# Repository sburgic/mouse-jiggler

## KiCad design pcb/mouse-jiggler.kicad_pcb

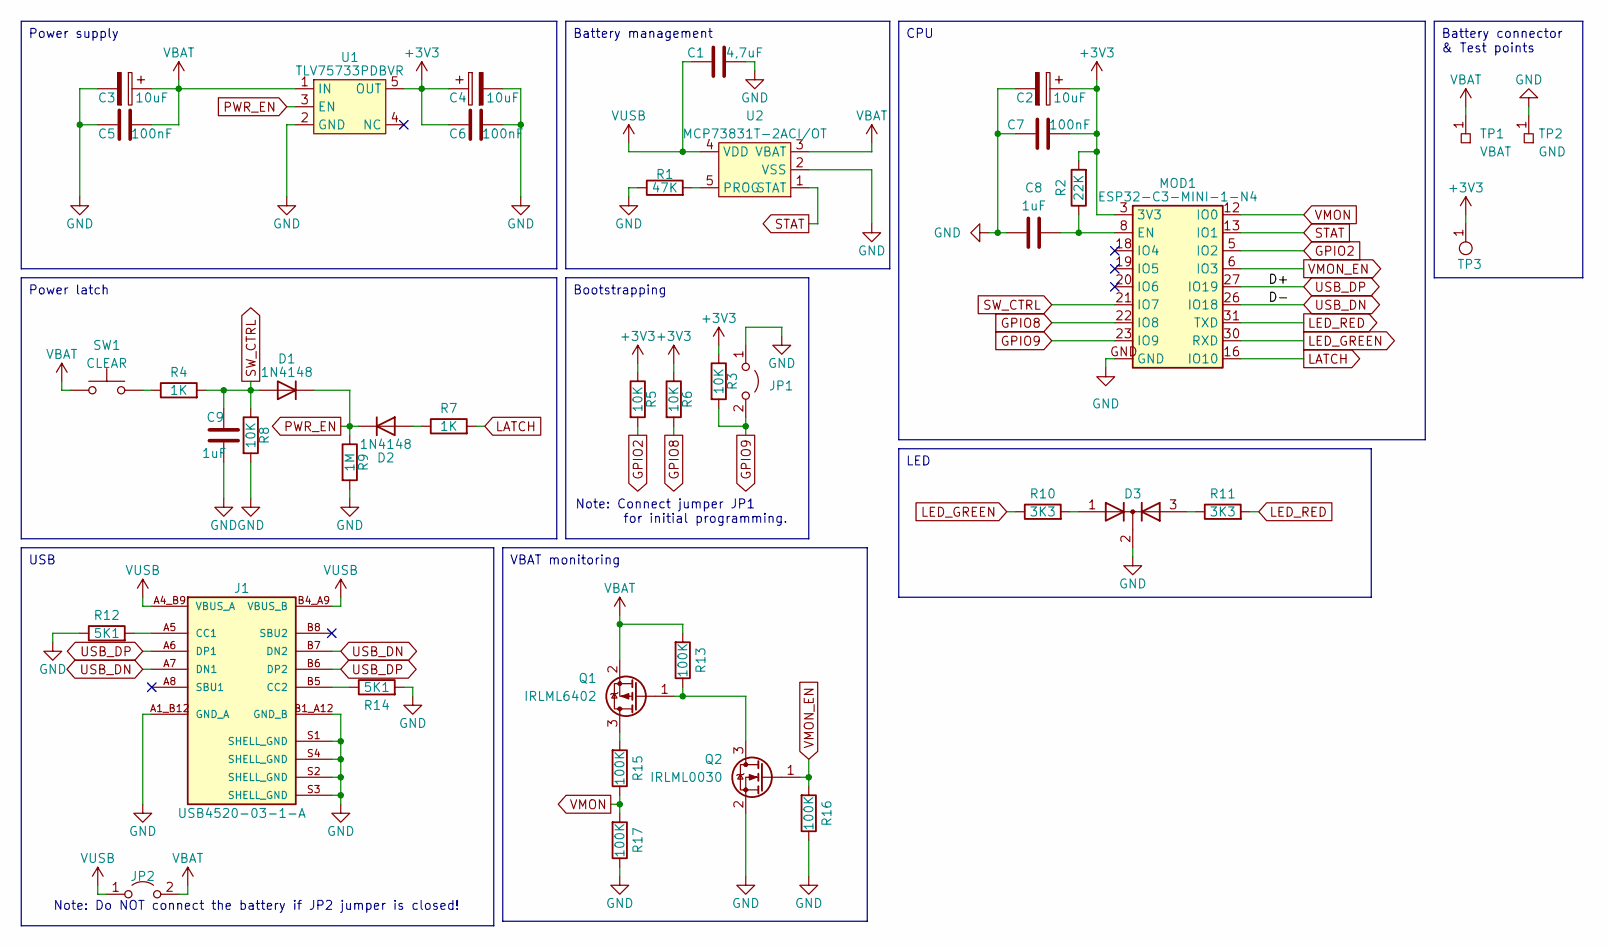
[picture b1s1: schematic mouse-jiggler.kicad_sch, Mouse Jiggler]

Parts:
C1: 4,7uF; C_0603_1608Metric_Pad1.08x0.95mm_HandSolder
C2, C3, C4: 10uF; C_0603_1608Metric_Pad1.08x0.95mm_HandSolder
C5, C6, C7: 100nF; C_0603_1608Metric_Pad1.08x0.95mm_HandSolder
C8, C9: 1uF; C_0603_1608Metric_Pad1.08x0.95mm_HandSolder
D1, D2: 1N4148; D_SOD-323_HandSoldering
D3: GREEN/RED; TH GENERIC LED 3MM DUAL (RED 3D)
J1: USB4520-03-1-A; SMD USB4520-03-1-A
JP1, JP2: Jumper_2_Open; SolderJumper-2_P1.3mm_Open_RoundedPad1.0x1.5mm
MOD1: ESP32-C3-MINI-1-N4; SMD ESP32-C3-MINI-1-N4
Q1: IRLML6402; SOT-23
Q2: IRLML0030; SOT-23
R1: 47K; R_0603_1608Metric_Pad0.98x0.95mm_HandSolder
R2: 22K; R_0603_1608Metric_Pad0.98x0.95mm_HandSolder
R3, R5, R6, R8: 10K; R_0603_1608Metric_Pad0.98x0.95mm_HandSolder
R4, R7: 1K; R_0603_1608Metric_Pad0.98x0.95mm_HandSolder
R9: 1M; R_0603_1608Metric_Pad0.98x0.95mm_HandSolder
R10, R11: 3K3; R_0603_1608Metric_Pad0.98x0.95mm_HandSolder
R12, R14: 5K1; R_0603_1608Metric_Pad0.98x0.95mm_HandSolder
R13, R15, R16, R17: 100K; R_0603_1608Metric_Pad0.98x0.95mm_HandSolder
SW1: CLEAR; SMD GENERIC 2-PIN 3.6x6x2.5
TP1: VBAT; TestPoint_THTPad_1.5x1.5mm_Drill0.7mm
TP2: GND; TestPoint_THTPad_1.5x1.5mm_Drill0.7mm
TP3: TP-ROUND-SMD-2MM; TestPoint_Pad_D1.0mm
U1: TLV75733PDBVR; SOT-23-5_HandSoldering
U2: MCP73831T-2ACI/OT; TSOP-5_1.65x3.05mm_P0.95mm

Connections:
+3V3: C2.1, C4.1, C6.2, C7.1, MOD1.3 (3V3), R2.2, R3.1, R5.1, R6.1, TP3.1, U1.5 (OUT)
GND: C1.2, C2.2, C3.2, C4.2, C5.1, C6.1, C7.2, C8.1, C9.2, D3.2 (K), J1.A1_B12 (GND_A), J1.B1_A12 (GND_B), J1.S1 (SHELL_GND), J1.S2 (SHELL_GND), J1.S3 (SHELL_GND), J1.S4 (SHELL_GND), JP1.1 (A), MOD1.GND, Q2.2 (S), R1.1, R8.2, R9.2, R12.1, R14.2, R16.1, R17.1, TP2.1, U1.2 (GND), U2.2 (VSS)
GPIO2: MOD1.5 (IO2), R5.2
GPIO8: MOD1.22 (IO8), R6.2
GPIO9: JP1.2 (B), MOD1.23 (IO9), R3.2
LATCH: MOD1.16 (IO10), R7.2
LED_GREEN: MOD1.30 (RXD), R10.1
LED_RED: MOD1.31 (TXD), R11.2
unnamed: D2.2 (A), R7.1
unnamed: D3.1 (A), R10.2
unnamed: D3.3 (A), R11.1
unnamed: J1.A5 (CC1), R12.2
unnamed: J1.B5 (CC2), R14.1
unnamed: C8.2, MOD1.8 (EN), R2.1
unnamed: Q1.3 (D), R15.2
unnamed: Q1.1 (G), Q2.3 (D), R13.1
unnamed: R4.1, SW1.1
unnamed: R1.2, U2.5 (PROG)
PWR_EN: D1.1 (K), D2.1 (K), R9.1, U1.3 (EN)
STAT: MOD1.13 (IO1), U2.1 (STAT)
SW_CTRL: C9.1, D1.2 (A), MOD1.21 (IO7), R4.2, R8.1
USB_DN: J1.A7 (DN1), J1.B7 (DN2), MOD1.26 (IO18)
USB_DP: J1.A6 (DP1), J1.B6 (DP2), MOD1.27 (IO19)
VBAT: C3.1, C5.2, JP2.2 (B), Q1.2 (S), R13.2, SW1.2, TP1.1, U1.1 (IN), U2.3 (VBAT)
VMON: MOD1.12 (IO0), R15.1, R17.2
VMON_EN: MOD1.6 (IO3), Q2.1 (G), R16.2
VUSB: C1.1, J1.A4_B9 (VBUS_A), J1.B4_A9 (VBUS_B), JP2.1 (A), U2.4 (VDD)

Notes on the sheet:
Note: Do NOT connect the battery if JP2 jumper is closed!
Note: Connect jumper JP1 for initial programming.
Battery connector & Test points
Battery management
CPU
Power latch
VBAT monitoring
Bootstrapping
Power supply
USB
LED

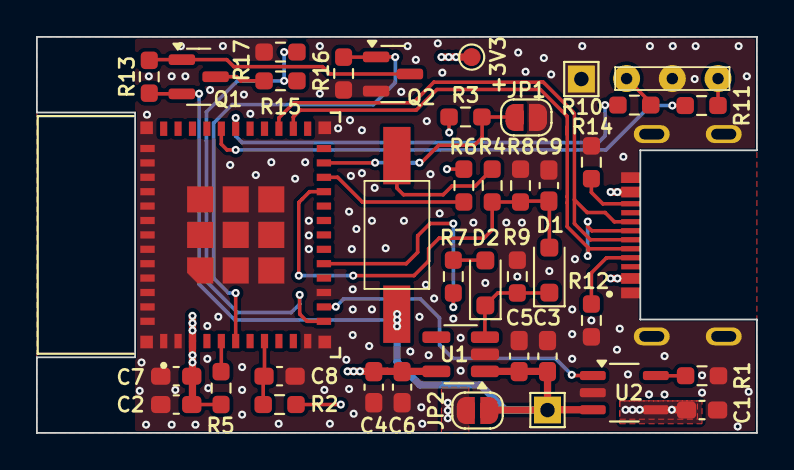
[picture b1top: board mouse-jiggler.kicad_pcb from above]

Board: 4 copper layers, 40.0 x 22.0 mm, 41 parts (0 on the bottom side), 27 nets.

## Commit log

2026-01-05 Add PCB files
2026-01-05 Code refactor
